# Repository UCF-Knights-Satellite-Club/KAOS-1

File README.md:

# KAOS-1 Project
KAOS (Knight Air Observer Satellite)-1 is a 4U CubeSat that will be launched on a weather balloon to study atmospheric chemistry.

## Hardware
TODO: add hardware description

## Software
This project utilizes the Arduino ecosystem on a **DOIT ESP32 DEVKIT V1**. Unless stated otherwise, all libraries can be found in the Arduino IDE Library Manager.

### Prerequisites
- **Arduino ESP32 Core** ([installation instructions](https://docs.espressif.com/projects/arduino-esp32/en/latest/installing.html))
- **Adafruit BMP3XX Library** by Adafruit
- **Adafruit SCD30** by Adafruit
- **RTClib** by Adafruit
- **Adafruit MMA8451 Library** by Adafruit
- **Arducam_Mega** by Arducam

### Explanation
The flight software has five states. The first state is `CALIBRATION` which averages several altitude readings to determine a launch altitude. Next is `PREFLIGHT` which runs when KAOS-1 is on the ground and waiting to be released on the balloon. High acceleration or breaking an altitude threshold will move to the `ASCENT` state. In this state, KAOS-1 monitors acceleration to determine when it is in free fall. In free fall, the accelerometer will read close to zero. Once this condition is met, the state moves to `FREEFALL` where altitude is compared to the deployment altitude. Once deployment altitude is reached, the a buzzer is enabled and the state switches to `LANDING`.

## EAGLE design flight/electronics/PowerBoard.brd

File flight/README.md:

# Flight Software
This folder is for storing flight software (the programs that our flight board will run for all necessary functions)

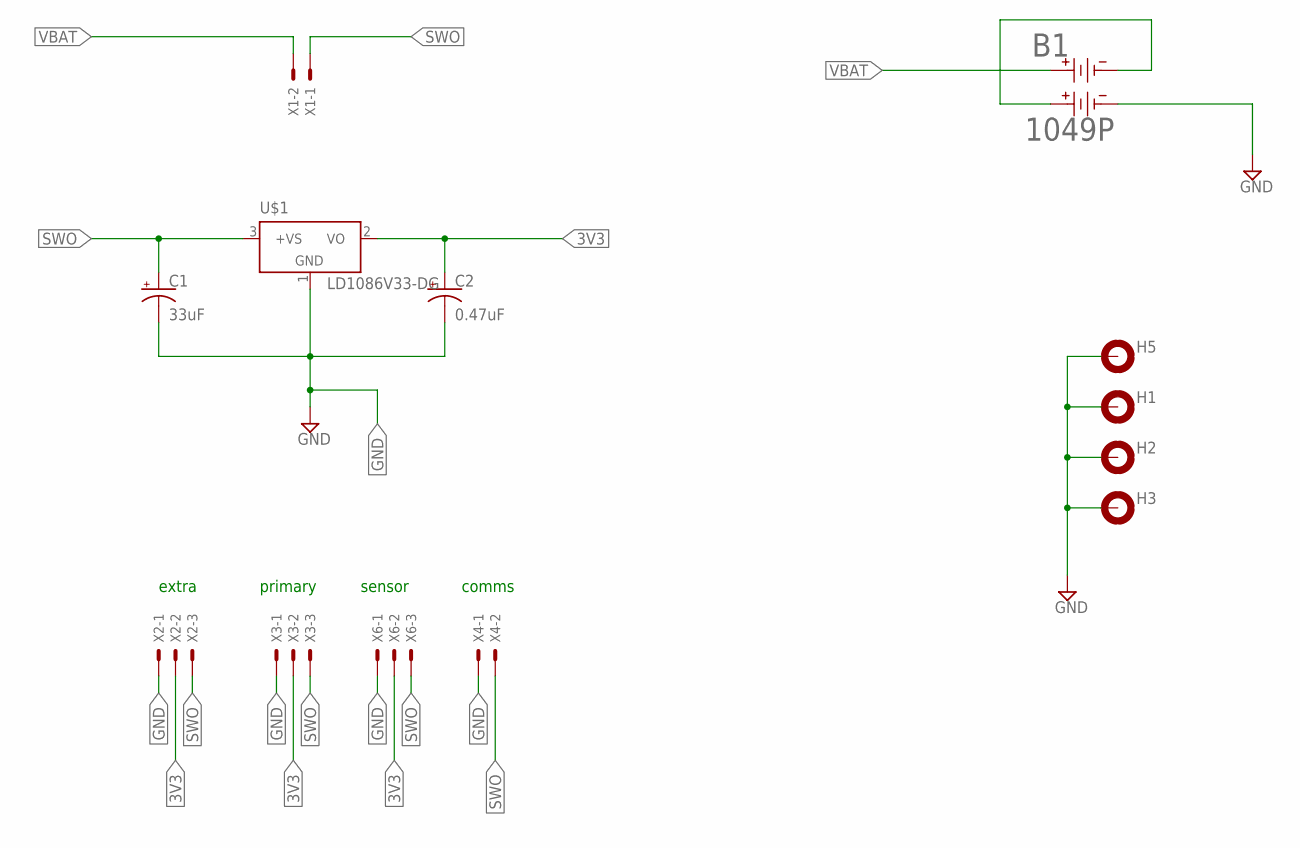
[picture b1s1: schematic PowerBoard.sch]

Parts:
B1: 1049P; 1049P_KEY
C1: 33uF; E2,5-5
C2: 0.47uF; E2,5-5
H1, H2, H3, H5: MOUNT-PAD-ROUND3.0; 3,0-PAD
U$1: LD1086V33-DG; TO220H
X1, X4: JST-XH-02-PIN; JST-XH_S2B
X2, X3, X6: JST-XH-03-PIN; JST-XH_S3B

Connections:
3V3: C2.+, U$1.2 (VO), X2.PIN2, X3.PIN2, X6.PIN2
GND: B1.3, C1.-, C2.-, H1.B3,0, H2.B3,0, H3.B3,0, H5.B3,0, U$1.1 (GND), X2.PIN1, X3.PIN1, X4.PIN1, X6.PIN1
unnamed: B1.2, B1.4
SWO: C1.+, U$1.3 (+VS), X1.PIN1, X2.PIN3, X3.PIN3, X4.PIN2, X6.PIN3
VBAT: B1.1, X1.PIN2

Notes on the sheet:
extra
primary
sensor
comms

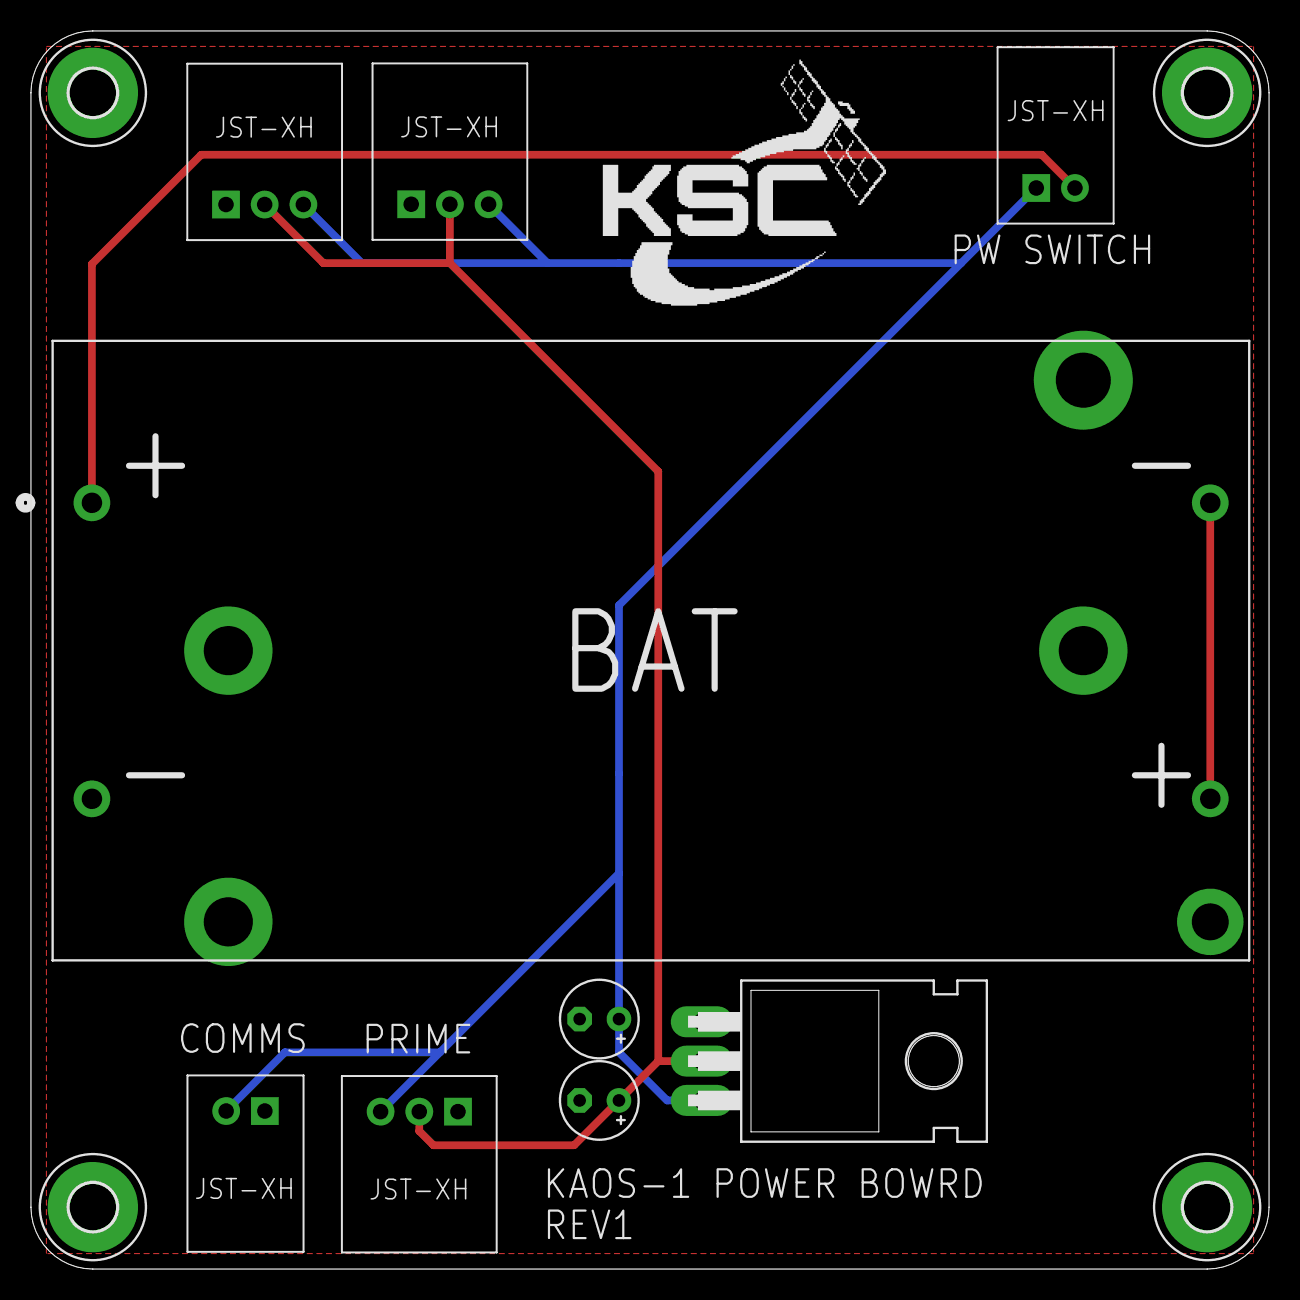
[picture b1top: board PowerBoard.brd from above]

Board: 2 copper layers, 80.0 x 80.0 mm, 13 parts (0 on the bottom side), 5 nets.

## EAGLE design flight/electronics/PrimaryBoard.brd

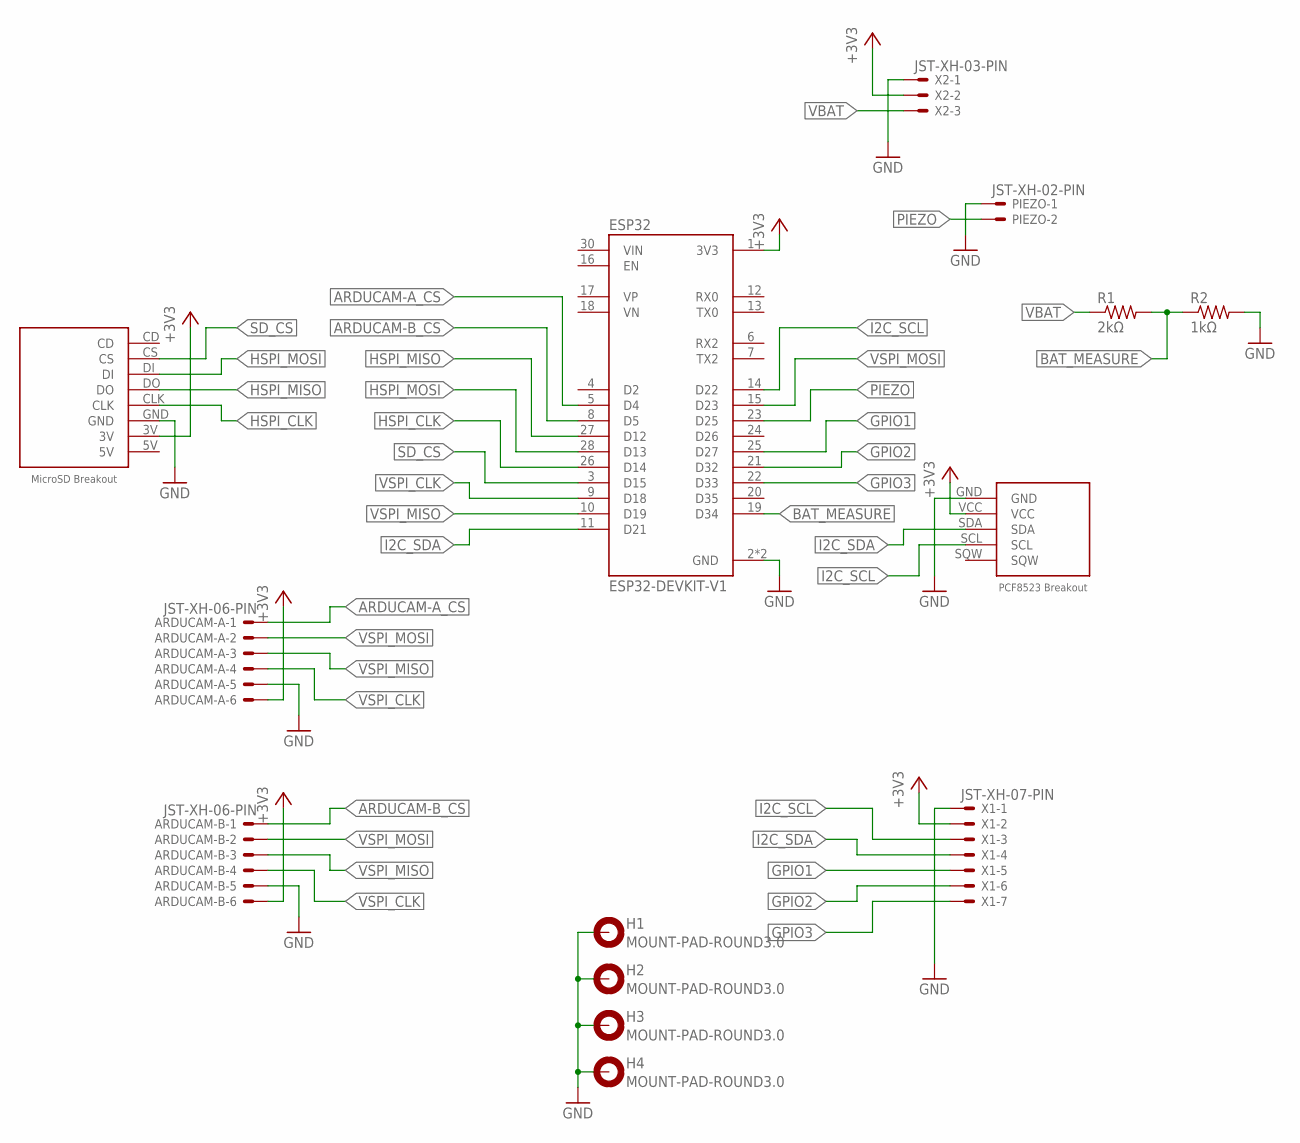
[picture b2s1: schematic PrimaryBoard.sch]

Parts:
ARDUCAM-A: JST-XH-06-PIN; JST-XH_S6B
ARDUCAM-B: JST-XH-06-PIN; JST-XH_S6B
ESP32: ESP32-DEVKIT-V1; MODULE_ESP32_DEVKIT_V1
H1, H2, H3, H4: MOUNT-PAD-ROUND3.0; 3,0-PAD
PIEZO: JST-XH-02-PIN; JST-XH_S2B
R1: 2kΩ; 0207/10
R2: 1kΩ; 0207/10
U$1: MICROSDBREAKOUT5V
U$2: PCF8523BREAKOUT
X1: JST-XH-07-PIN; JST-XH_S7B
X2: JST-XH-03-PIN; JST-XH_S3B

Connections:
+3V3: ARDUCAM-A.PIN6, ARDUCAM-B.PIN6, ESP32.1 (3V3), U$1.3V, U$2.VCC, X1.PIN2, X2.PIN2
ARDUCAM-A_CS: ARDUCAM-A.PIN1, ESP32.5 (D4)
ARDUCAM-B_CS: ARDUCAM-B.PIN1, ESP32.8 (D5)
BAT_MEASURE: ESP32.19 (D34), R1.2, R2.1
GND: ARDUCAM-A.PIN5, ARDUCAM-B.PIN5, ESP32.2 (GND), ESP32.29 (GND), H1.B3,0, H2.B3,0, H3.B3,0, H4.B3,0, PIEZO.PIN1, R2.2, U$1.GND, U$2.GND, X1.PIN1, X2.PIN1
GPIO1: ESP32.25 (D27), X1.PIN5
GPIO2: ESP32.21 (D32), X1.PIN6
GPIO3: ESP32.22 (D33), X1.PIN7
HSPI_CLK: ESP32.26 (D14), U$1.CLK
HSPI_MISO: ESP32.27 (D12), U$1.DO
HSPI_MOSI: ESP32.28 (D13), U$1.DI
I2C_SCL: ESP32.14 (D22), U$2.SCL, X1.PIN3
I2C_SDA: ESP32.11 (D21), U$2.SDA, X1.PIN4
PIEZO: ESP32.23 (D25), PIEZO.PIN2
SD_CS: ESP32.3 (D15), U$1.CS
VBAT: R1.1, X2.PIN3
VSPI_CLK: ARDUCAM-A.PIN4, ARDUCAM-B.PIN4, ESP32.9 (D18)
VSPI_MISO: ARDUCAM-A.PIN3, ARDUCAM-B.PIN3, ESP32.10 (D19)
VSPI_MOSI: ARDUCAM-A.PIN2, ARDUCAM-B.PIN2, ESP32.15 (D23)

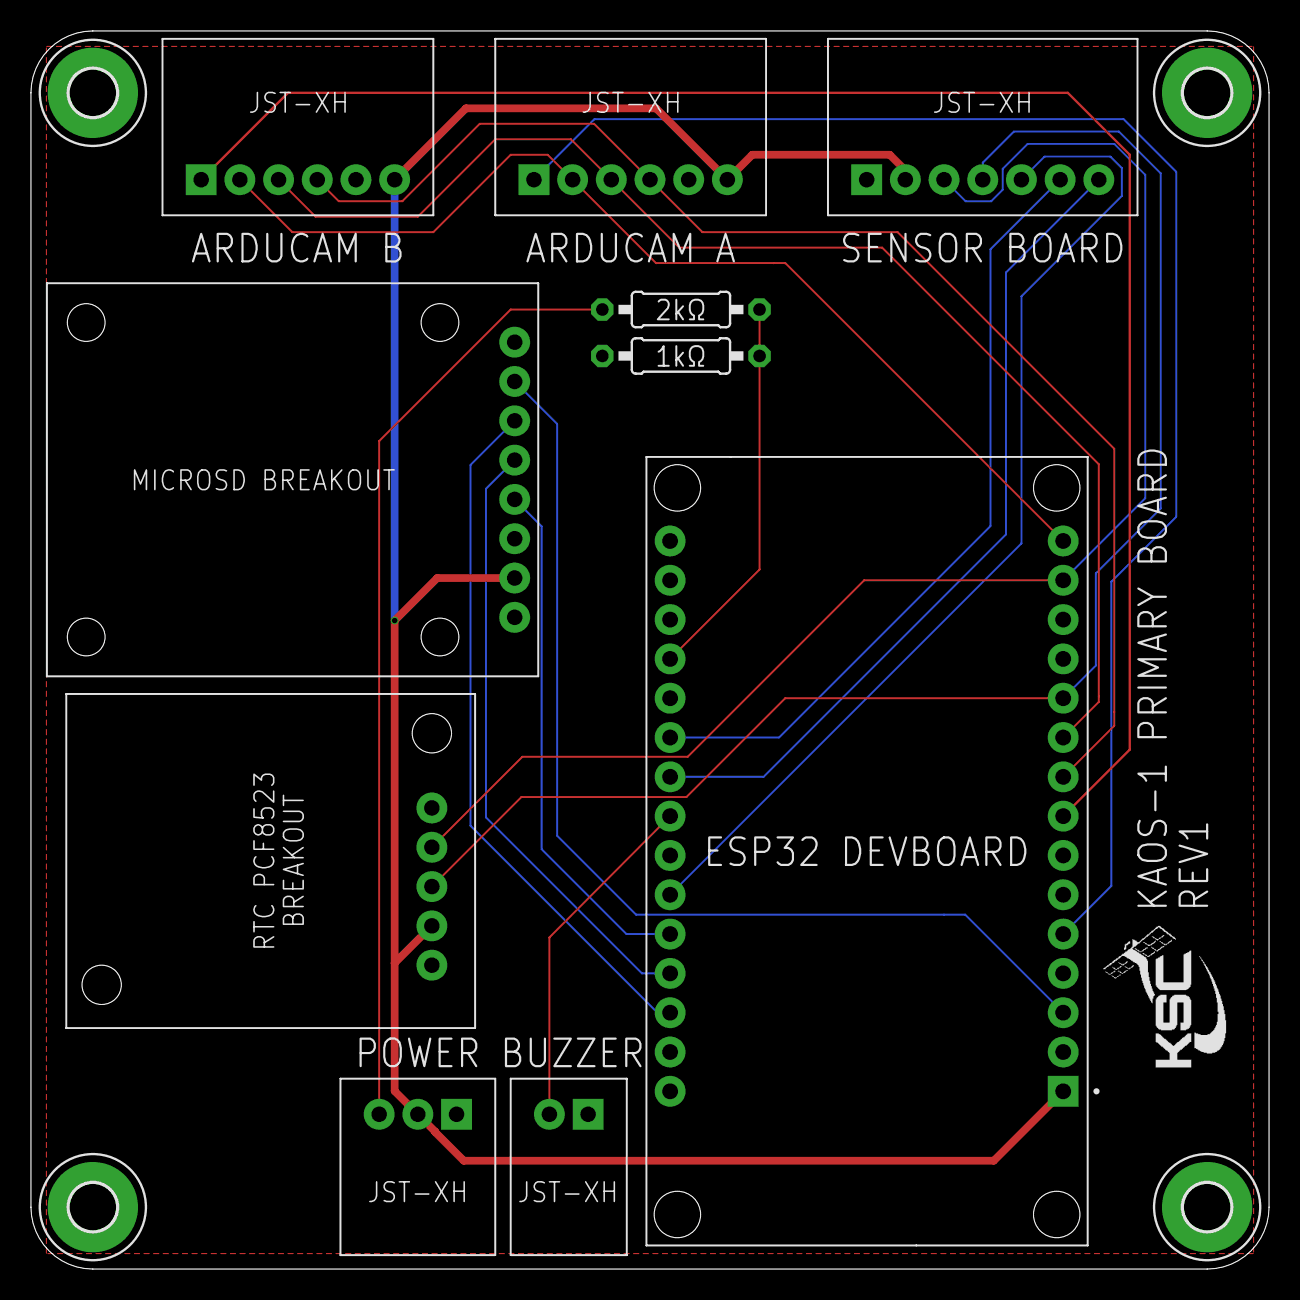
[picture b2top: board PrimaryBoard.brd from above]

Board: 2 copper layers, 80.0 x 80.0 mm, 14 parts (0 on the bottom side), 19 nets.

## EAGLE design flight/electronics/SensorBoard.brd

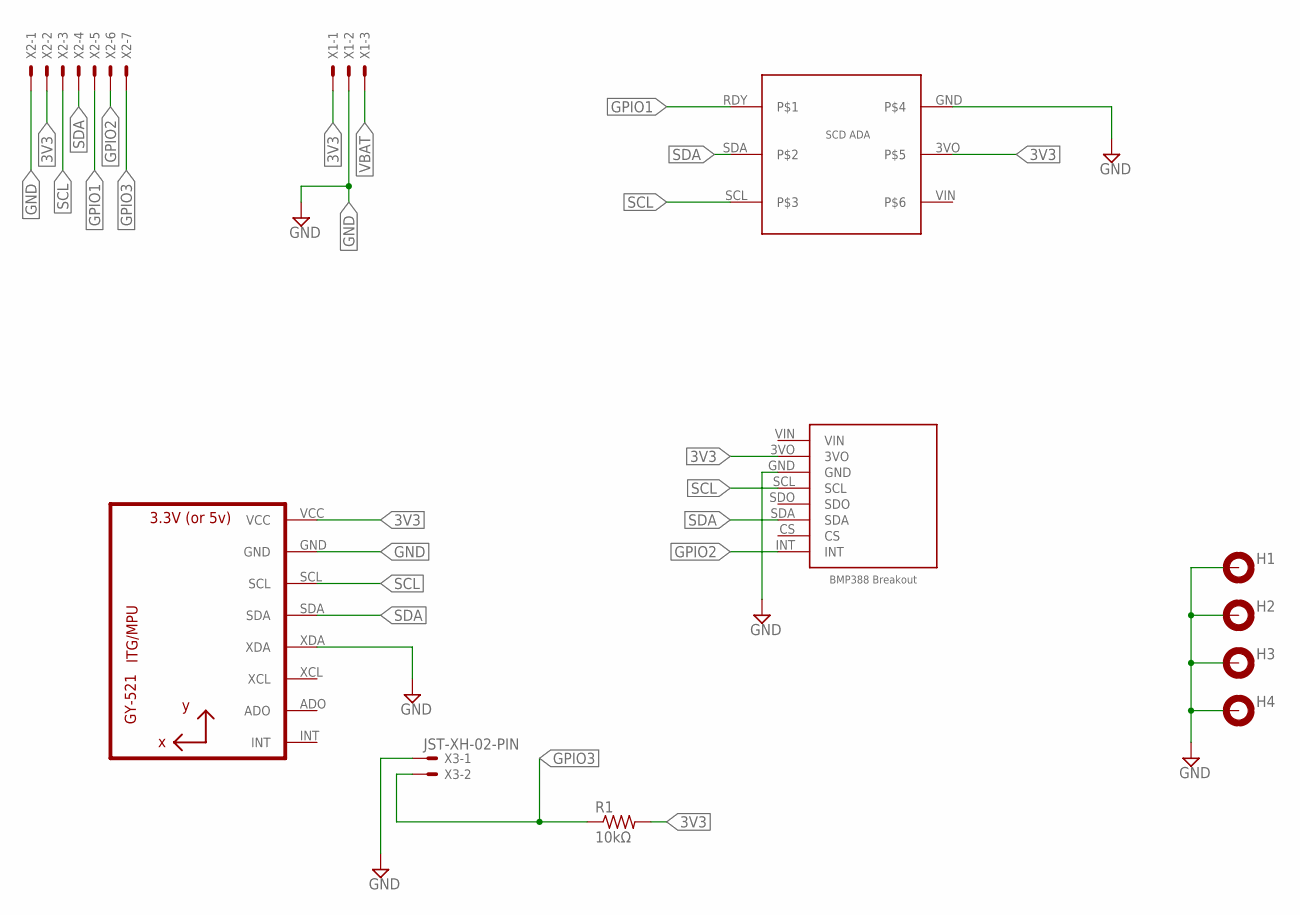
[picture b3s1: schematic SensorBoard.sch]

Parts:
H1, H2, H3, H4: MOUNT-PAD-ROUND3.0; 3,0-PAD
R1: 10kΩ; 0204/7
U1: GY-521MPU6050; GY-521
U$2: BMP388BREAKOUT
U$6: SCD30_ADA
X1: JST-XH-03-PIN; JST-XH_S3B
X2: JST-XH-07-PIN; JST-XH_S7B
X3: JST-XH-02-PIN; JST-XH_S2B

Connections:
3V3: R1.2, U1.VCC, U$2.3VO, U$6.3VO, X1.PIN1, X2.PIN2
GND: H1.B3,0, H2.B3,0, H3.B3,0, H4.B3,0, U1.GND, U1.XDA, U$2.GND, U$6.GND, X1.PIN2, X2.PIN1, X3.PIN1
GPIO1: U$6.RDY, X2.PIN5
GPIO2: U$2.INT, X2.PIN6
GPIO3: R1.1, X2.PIN7, X3.PIN2
SCL: U1.SCL, U$2.SCL, U$6.SCL, X2.PIN3
SDA: U1.SDA, U$2.SDA, U$6.SDA, X2.PIN4
VBAT: X1.PIN3

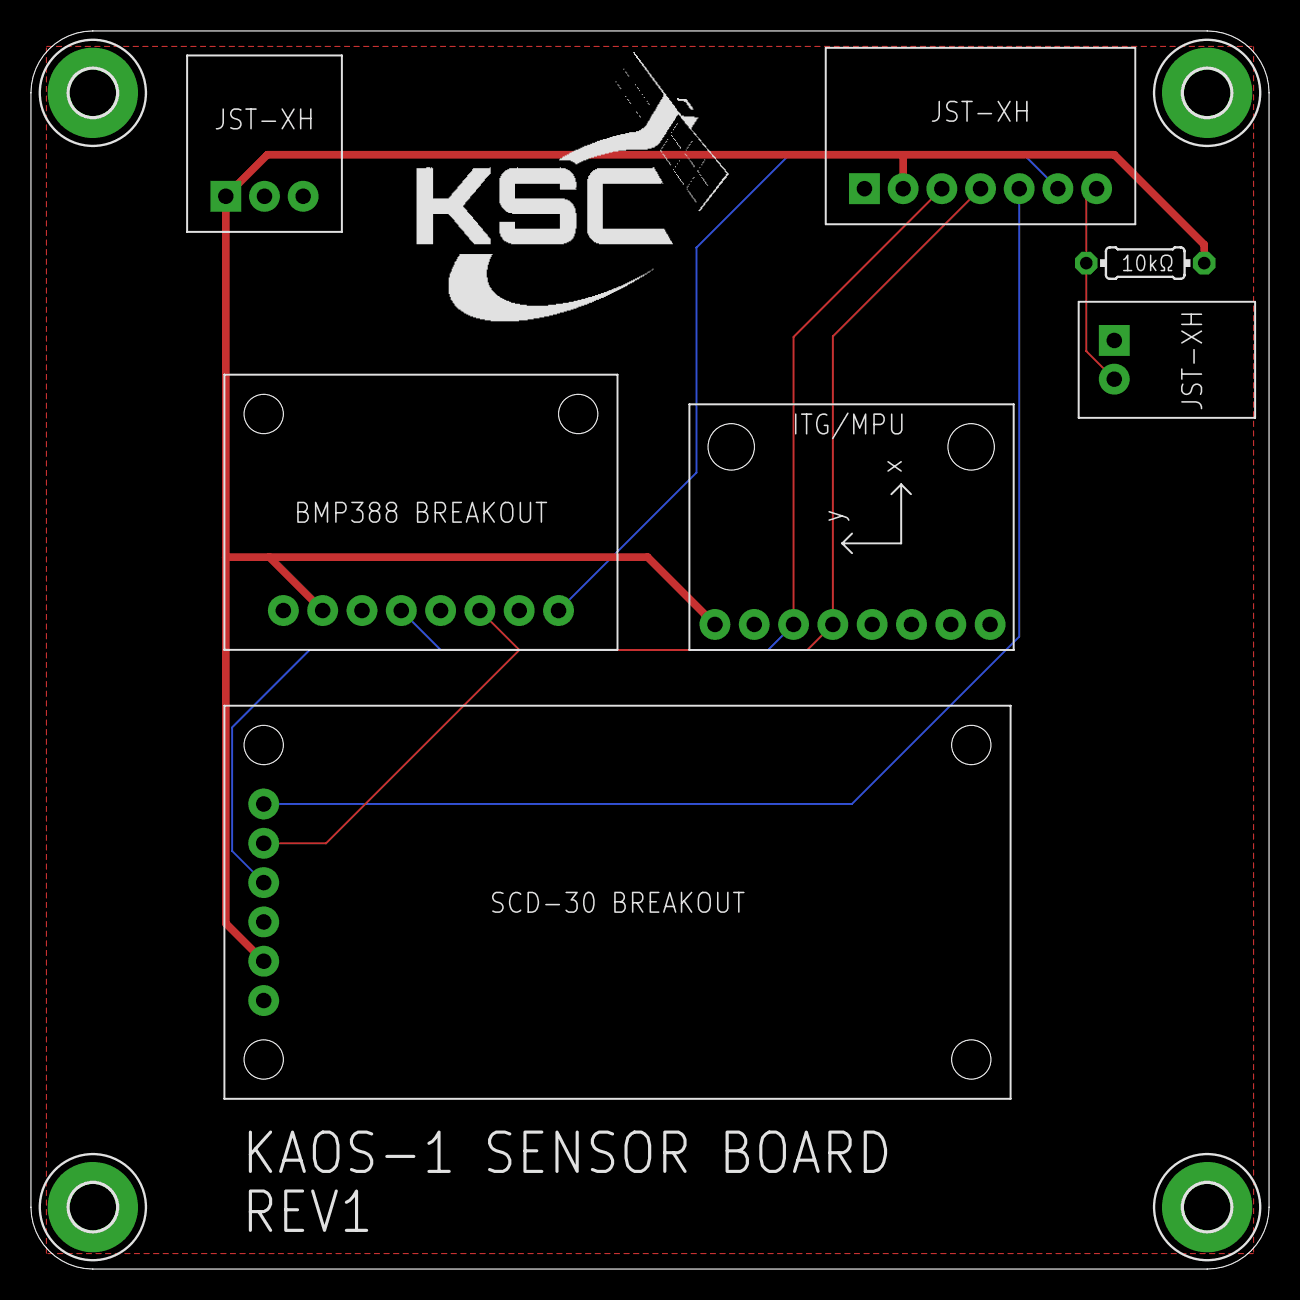
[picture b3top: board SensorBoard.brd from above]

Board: 2 copper layers, 80.0 x 80.0 mm, 11 parts (0 on the bottom side), 7 nets.

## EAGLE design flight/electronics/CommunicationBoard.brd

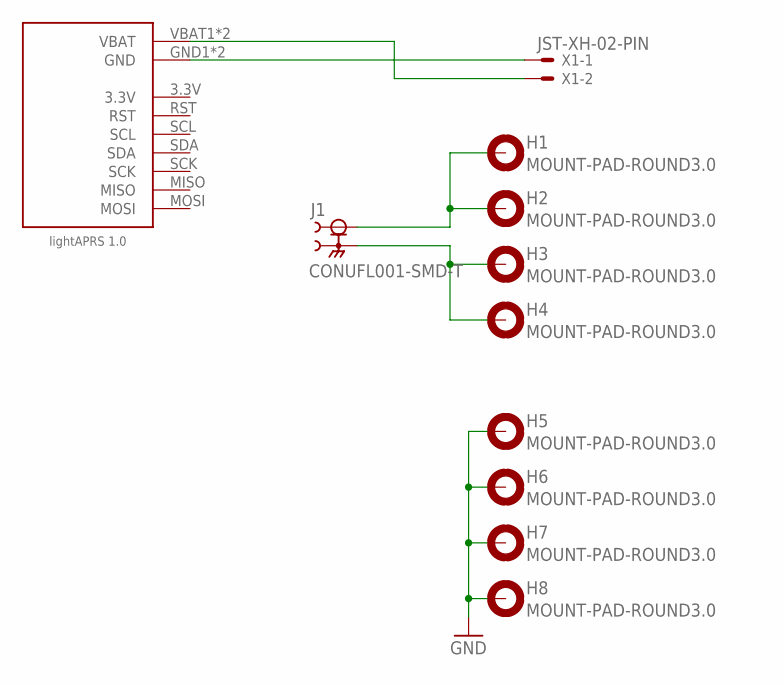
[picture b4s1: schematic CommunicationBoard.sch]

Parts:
H1, H2, H3, H4, H5, H6, H7, H8: MOUNT-PAD-ROUND3.0; 3,0-PAD
J1: CONUFL001-SMD-T; LINX_CONUFL001-SMD-T
U$1: LIGHTAPRS
X1: JST-XH-02-PIN; JST-XH_S2B

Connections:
GND: H5.B3,0, H6.B3,0, H7.B3,0, H8.B3,0, U$1.GND1 (GND), U$1.GND2 (GND), X1.PIN1
SIG+: H1.B3,0, H2.B3,0, J1.1
SIG-: H3.B3,0, H4.B3,0, J1.2, J1.3 (2)
VBAT: U$1.VBAT1 (VBAT), U$1.VBAT2 (VBAT), X1.PIN2

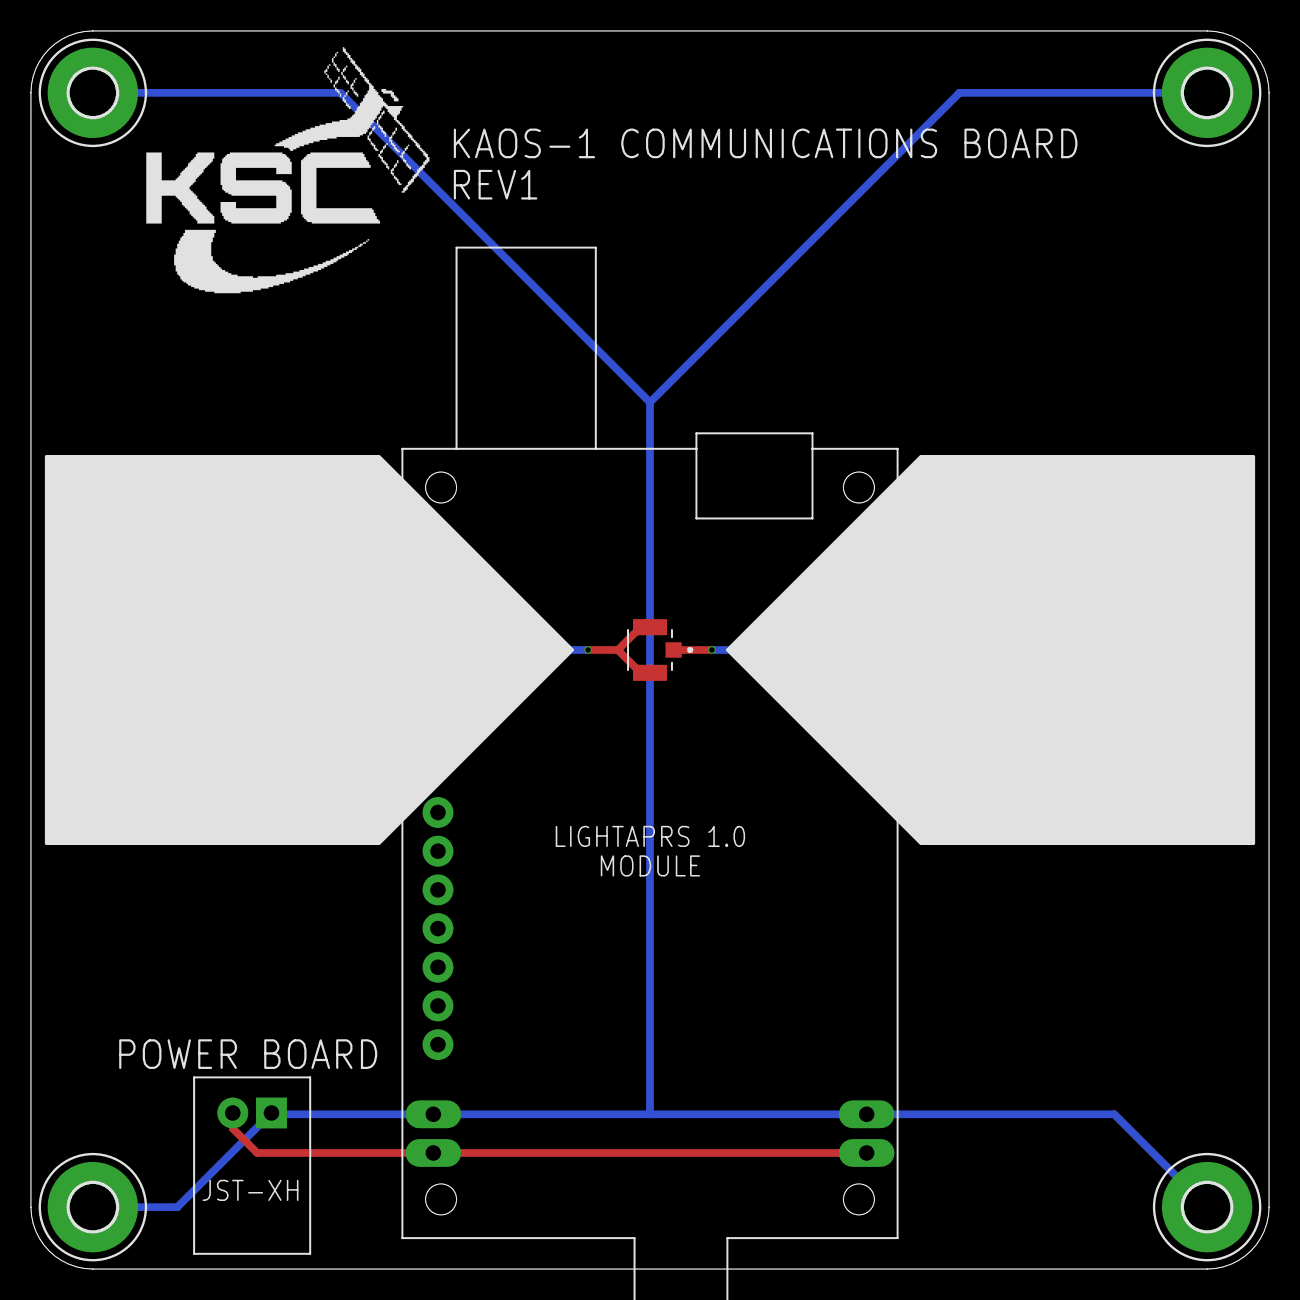
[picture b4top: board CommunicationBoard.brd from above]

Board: 2 copper layers, 80.0 x 80.0 mm, 11 parts (0 on the bottom side), 4 nets.

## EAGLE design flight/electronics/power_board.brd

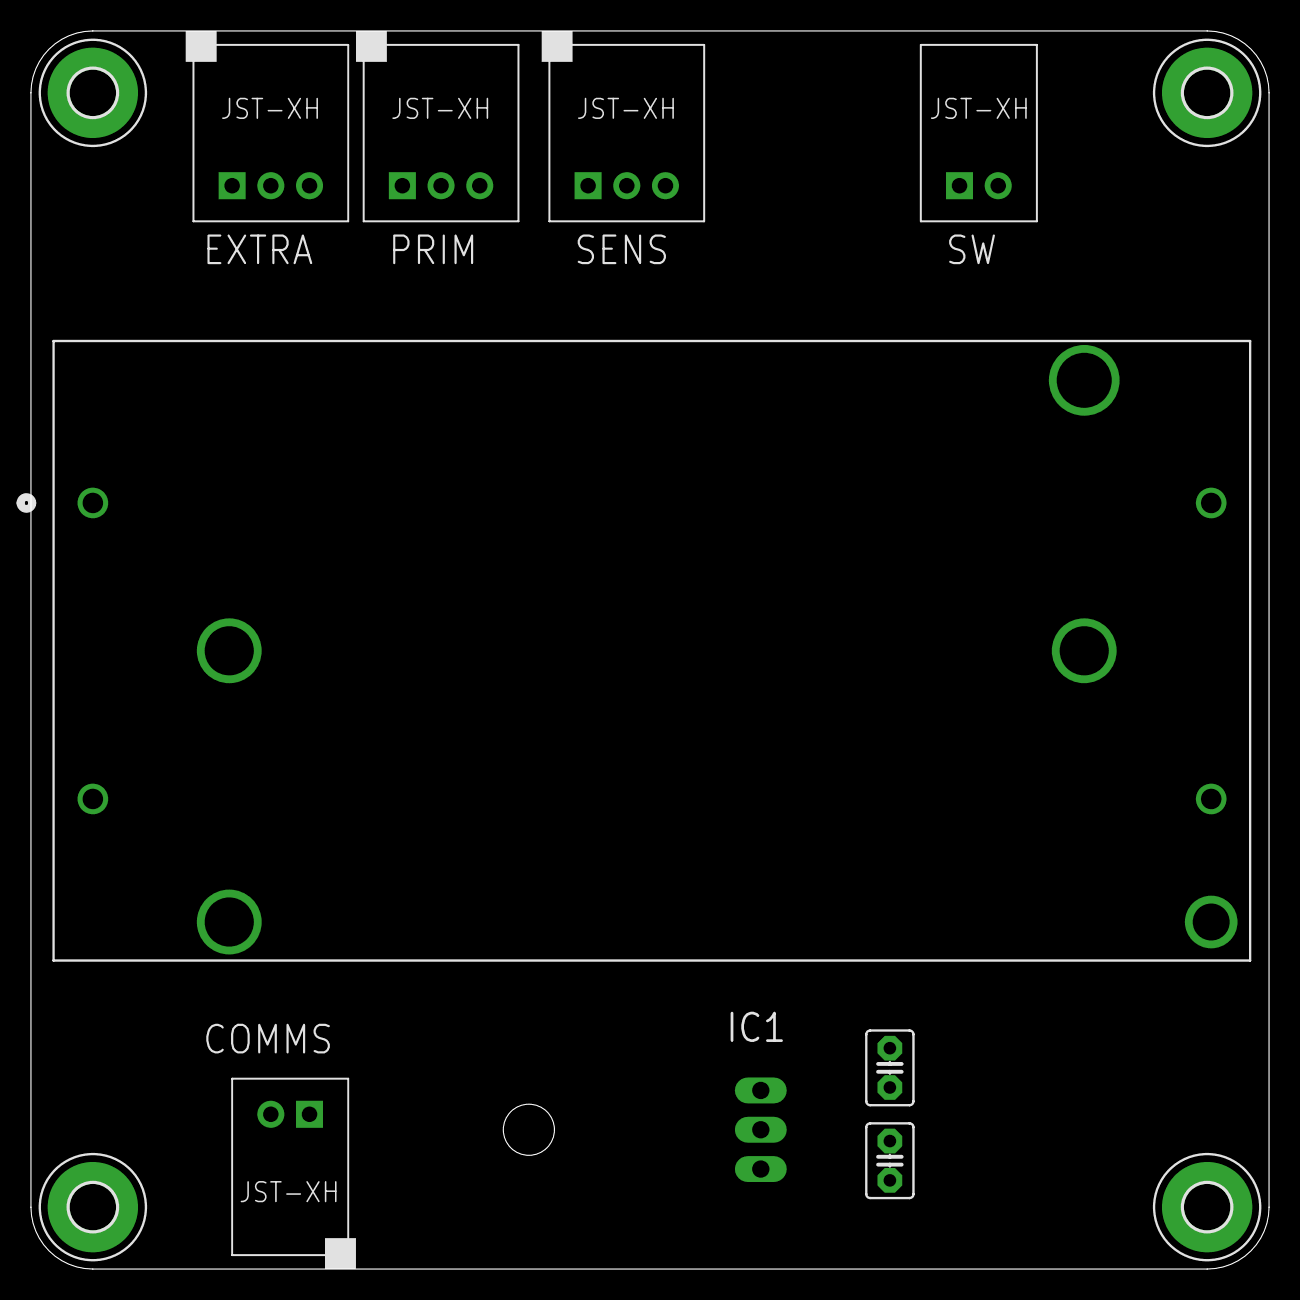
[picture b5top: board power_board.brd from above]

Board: 2 copper layers, 80.0 x 80.0 mm, 13 parts (1 on the bottom side), 6 nets, no tracks yet.

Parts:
B1: 1049P; 1049P_KEY
C1: 0.33uF; C2.5-3
C2: 0.1uF; C2.5-3
H1, H2, H3, H4: MOUNT-PAD-ROUND3.0; 3,0-PAD
IC1: 7808T; TO220H
X1, X4: JST-XH-02-PIN; JST-XH_S2B
X2, X3, X6: JST-XH-03-PIN; JST-XH_S3B

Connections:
3V3: C2.1, IC1.3, X2.PIN2, X3.PIN2, X6.PIN2
GND: C1.2, C2.2, IC1.2, X2.PIN1, X3.PIN1, X4.PIN1, X6.PIN1
unnamed: B1.2, B1.4
unnamed: H1.B3,0, H2.B3,0, H3.B3,0, H4.B3,0
SWO: C1.1, IC1.1, X1.PIN1
VBAT: B1.1, X1.PIN2, X2.PIN3, X3.PIN3, X4.PIN2, X6.PIN3

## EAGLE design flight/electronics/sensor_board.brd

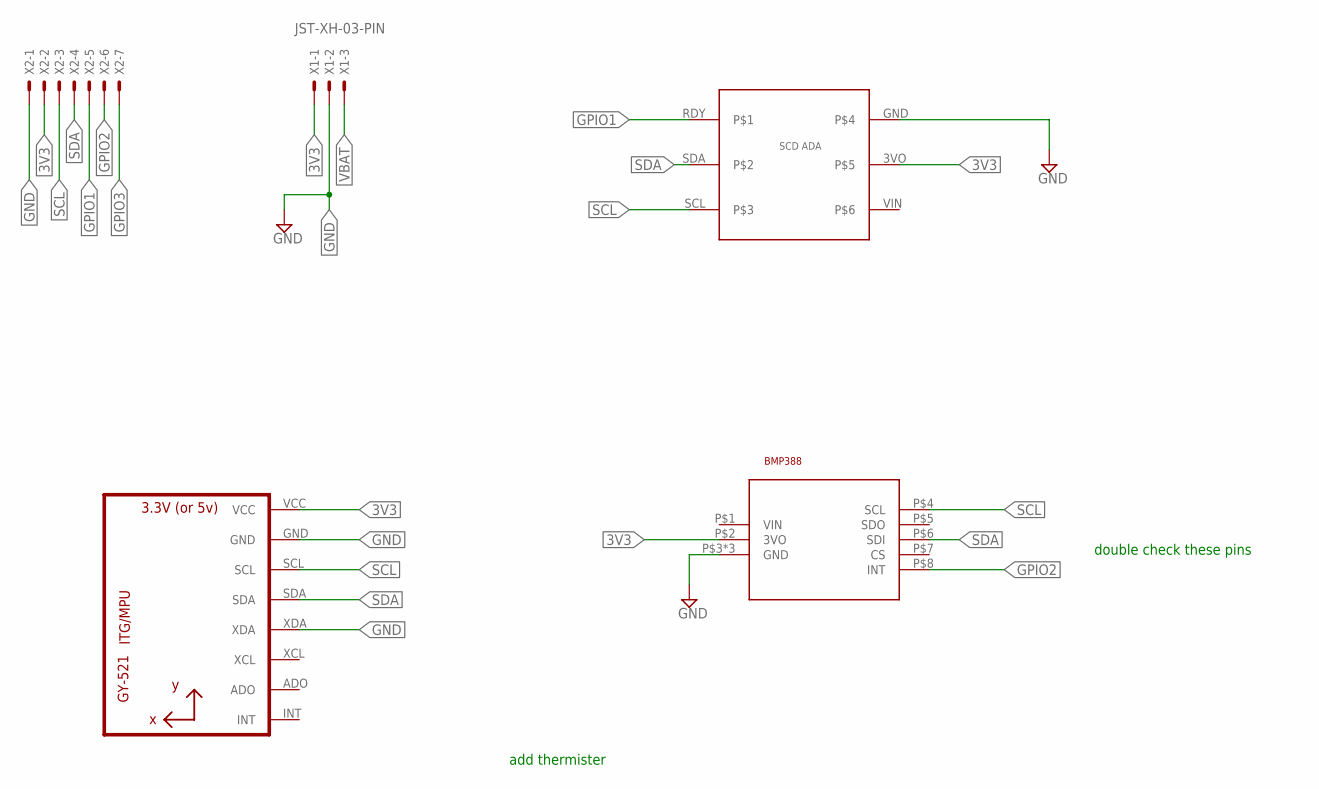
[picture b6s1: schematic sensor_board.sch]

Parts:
U1: GY-521MPU6050; GY-521
U$1: BMP388_QT
U$6: SCD30_ADA
X1: JST-XH-03-PIN; JST-XH_S3B
X2: JST-XH-07-PIN; JST-XH_S7B

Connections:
3V3: U1.VCC, U$1.P$2 (3VO), U$6.3VO, X1.PIN1, X2.PIN2
GND: U1.GND, U1.XDA, U$1.P$3 (GND), U$1.P$9 (GND), U$1.P$10 (GND), U$6.GND, X1.PIN2, X2.PIN1
GPIO1: U$6.RDY, X2.PIN5
GPIO2: U$1.P$8 (INT), X2.PIN6
GPIO3: X2.PIN7
SCL: U1.SCL, U$1.P$4 (SCL), U$6.SCL, X2.PIN3
SDA: U1.SDA, U$1.P$6 (SDI), U$6.SDA, X2.PIN4
VBAT: X1.PIN3

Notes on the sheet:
double check these pins
add thermister

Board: 2 copper layers, 9 parts (4 on the bottom side), 6 nets, no tracks yet.

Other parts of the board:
U$2, U$3, U$4, U$5: 3,0

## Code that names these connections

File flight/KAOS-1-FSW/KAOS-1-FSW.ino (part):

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// Pin constants
#define CAM_CS_A 4
#define CAM_CS_B 5
#define HSPI_MISO 12
#define HSPI_MOSI 13
#define HSPI_CLK 14
#define SD_CS 15
#define VSPI_CLK 18
#define VSPI_MISO 19
#define I2C_SDA 21
#define I2C_SCL 22
#define VSPI_MOSI 23
#define BUZZER_PIN 25
#define SCD30_RDY 27
#define BMP388_INT 32
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
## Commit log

2023-03-04 Added flight folder
2023-03-04 added ground folder
2023-03-04 more folders added
2023-03-17 added kaos-0 files
2023-10-13 log sensor data to SD
2023-10-16 arduino console plot
2024-03-06 arudcam test code
2024-03-08 properly close sd card
2024-03-11 Create LightAPRS-hab.ino
    working test code for light aprs transciever
2024-03-20 primary board
2024-03-25 add lightaprs lib
2024-03-25 add eagle gitignore
2024-03-26 comms board
2024-03-26 primary board updates
2024-03-26 move antenna mounting holes
2024-03-26 round board corners
2024-03-26 remove thermal isolation
2024-03-26 dont push gerber zips
2024-03-26 shrink primary to 90mm
2024-03-26 update comms silkscreen
2024-03-27 add pcf8523 rtc
2024-03-27 primary board redesign
2024-03-27 franks files
2024-03-29 power/sensor
2024-03-29 final touches
2024-03-31 increase pad sizes
2024-03-31 final board tweaks
2024-03-31 rename boards
2024-03-31 ignore generated bitmap imports
2024-03-31 rev1 changes
2024-03-31 update caps on pb
2024-09-20 Created flatsat added TODOs
2024-09-27 new task
2024-10-19 match file and folder names
2024-10-19 update pin numbers
2024-10-22 get adc measurements
2024-11-18 camera code
2025-02-06 update TODO
2025-02-13 copy tsat0 fsw
2025-02-13 removed servo related code
    murder
2025-02-13 Changed log directory
2025-02-14 Details about libraries
    Added a description of what each library does and sorted them by groups of what they do.
2025-04-10 Update KAOS-1-FSW.ino
    Buzzer code version 1, started to comment on pin defines (WIP, pin 17 is not real)
2025-05-19 Update libraries in readme
2025-05-19 Copied pins from wiki
2025-05-19 Fixed compile
2025-05-28 Thermistor Implementation
2025-07-07 add board images
2025-07-07 fsw working on kaos platform
2025-07-07 Removed Averaging of Temperatures
2025-07-07 Fixed ADC code
2025-07-09 Fixed Folder Duplication
2025-07-14 Implemented battery voltage reader

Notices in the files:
parts and their libraries:
COPYRIGHT: Copyright (C) 2024 Ultra Librarian. All rights reserved.
